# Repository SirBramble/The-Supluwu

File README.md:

# The Supluwu

A voltage converter for 3D printers.

## Motivation

When modifying a 3D printer, sometimes you need smaller Voltages to run for example a Raspberry PI or 12V Fans. Smaller buck converter modules are useful but can be hard to mount or connect multiple devices to. The Supluwu is a small board meant to fix this.

## Features

The Supluwu features 2 Voltage rails with 5V and 12V. Each Voltage Rail is capable of 5A and is spread out over 3 Terminals. The Input of each Rail is Fused with a 20mmx5mm glass fuse. The Input Voltage can be anything from 14-30V, so the typical 24V power supply of a 3D printer works fine. Each Terminal has a indicator LED, that lights up, if the buck converter is working properly.

## Heat Management

Heat Produced by the Regulator is spread out to the PCB and can be carried away by the PCB mounted [14mmx14mm heat sinks](https://www.amazon.de/-/en/gp/product/B09DKJPZRX?th=1).

## Pictures

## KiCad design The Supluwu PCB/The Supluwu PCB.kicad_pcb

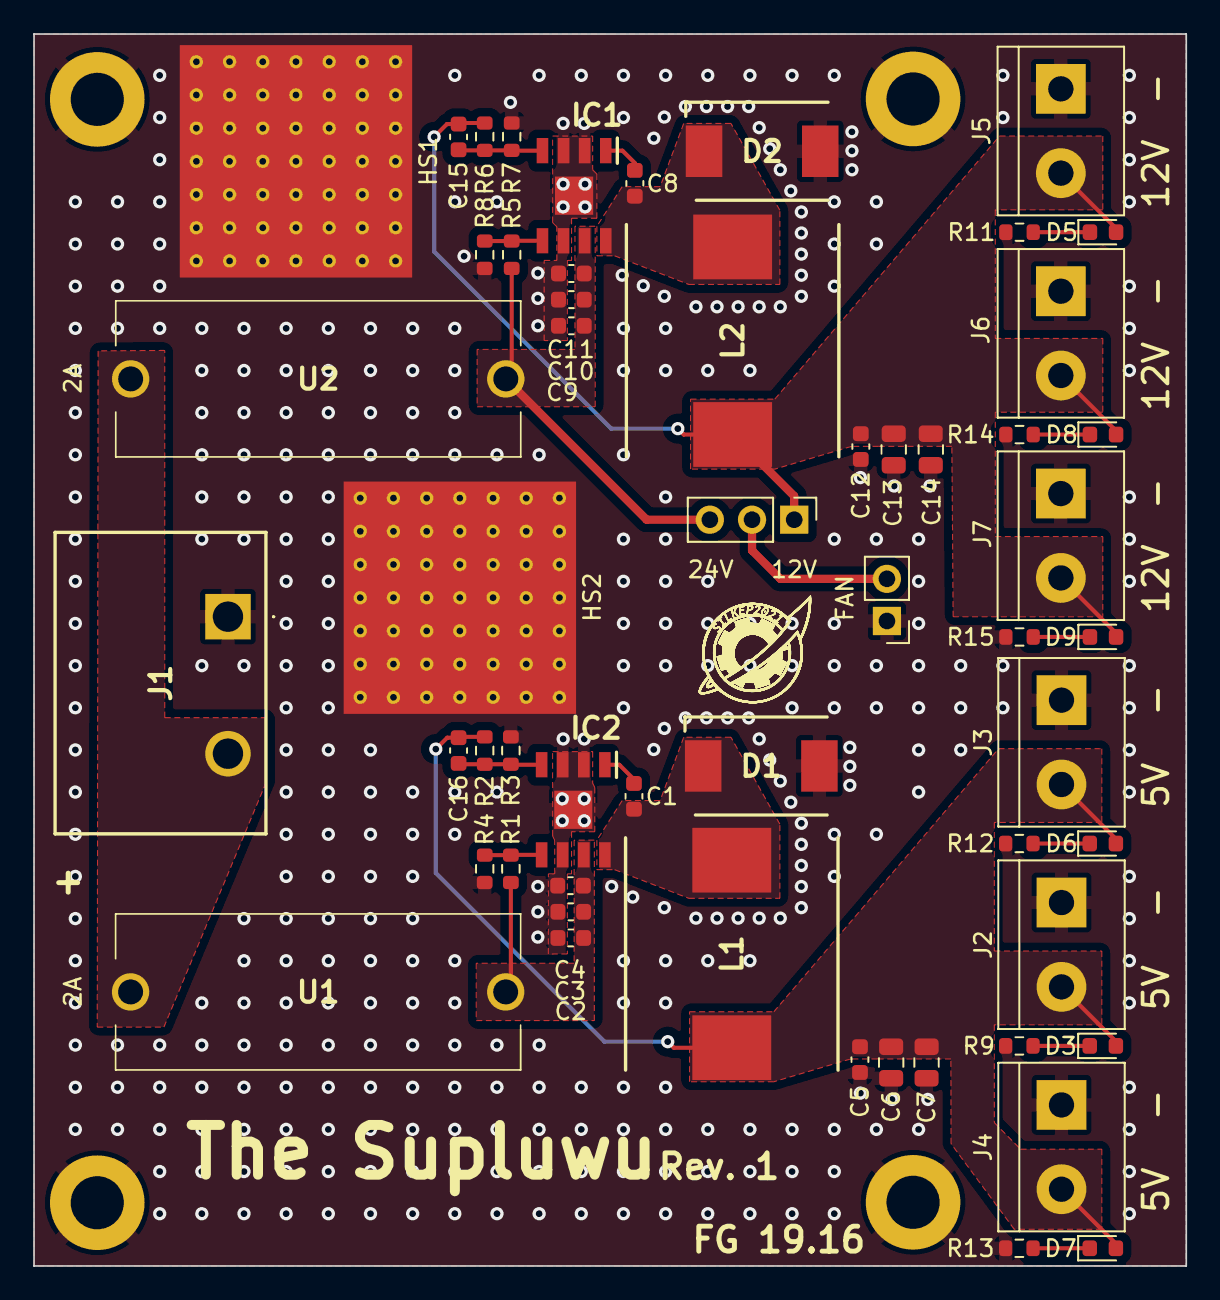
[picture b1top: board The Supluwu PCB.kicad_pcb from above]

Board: 2 copper layers, 69.4 x 74.2 mm, 59 parts (0 on the bottom side), 21 nets.

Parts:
C1, C8: 10nF; C_0603_1608Metric
C2, C3, C9, C10: 4u7; C_0603_1608Metric
C4, C5, C11, C12: 100n; C_0603_1608Metric
C6, C7, C13, C14: 22uF; C_0805_2012Metric
C15, C16: 82pF; C_0603_1608Metric
D1, D2: B550C-13-F; DIOM7959X250N
D3, D6, D7: LED_GREEN; LED_0603_1608Metric
D5, D8, D9: LED_Yellow; LED_0603_1608Metric
H1, H2, H3, H4: MountingHole_Pad; MountingHole_3.2mm_M3_ISO7380_Pad
HS1, HS2: Heatsink_Pad; 14x14mm PCB with VIA
IC1, IC2: RT6285GSP; SOIC127P600X175-9N
J1: 4DB-P107-02; 4DBP10702
J2, J3, J4, J5, J6, J7: 5V_OUT; TerminalBlock_bornier-2_P5.08mm
J8: V_Switch; PinHeader_1x03_P2.54mm_Vertical
J9: FAN; PinHeader_1x02_P2.54mm_Vertical
L1, L2: 15uH; INDPM140128X650N
R1, R4, R5, R8: DNP; R_0603_1608Metric
R2, R6: 100k; R_0603_1608Metric
R3: 31.6k; R_0603_1608Metric
R7: 11.3k; R_0603_1608Metric
R9, R12, R13: 1k; R_0603_1608Metric
R11, R14, R15: 3k3; R_0603_1608Metric
U1, U2: 0PTF0078P

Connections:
/5V Regulator/BOOT: C1.1, IC2.1 (BOOT)
/5V Regulator/EN: IC2.5 (EN), R1.2, R4.1
/5V Regulator/FB: C16.2, IC2.4 (FB), R2.2, R3.1
/5V Regulator/SW: C1.2, D1.1 (K), IC2.8 (SW), L1.1
/5V Regulator/VIN: C2.1, C3.1, C4.1, IC2.7 (VIN), R1.1, U1.2
/5V_OUT: C5.1, C6.1, C7.1, C16.1, D3.2 (A), D6.2 (A), D7.2 (A), J2.2, J3.2, J4.2, L1.2, R2.1
/12V Regulator/BOOT: C8.1, IC1.1 (BOOT)
/12V Regulator/EN: IC1.5 (EN), R5.2, R8.1
/12V Regulator/FB: C15.2, IC1.4 (FB), R6.2, R7.1
/12V Regulator/SW: C8.2, D2.1 (K), IC1.8 (SW), L2.1
/12V Regulator/VIN: C9.1, C10.1, C11.1, IC1.7 (VIN), J8.3, R5.1, U2.2
/12V_OUT: C12.1, C13.1, C14.1, C15.1, D5.2 (A), D8.2 (A), D9.2 (A), J5.2, J6.2, J7.2, J8.1, L2.2, R6.1
/24V_IN: J1.2, U1.1, U2.1
GND: C2.2, C3.2, C4.2, C5.2, C6.2, C7.2, C9.2, C10.2, C11.2, C12.2, C13.2, C14.2, D1.2 (A), D2.2 (A), H1.1, H2.1, H3.1, H4.1, HS1.1, HS2.1, IC1.2 (NC_1), IC1.3 (NC_2), IC1.6 (GND_1), IC1.9 (GND_2), IC2.2 (NC_1), IC2.3 (NC_2), IC2.6 (GND_1), IC2.9 (GND_2), J1.1, J2.1, J3.1, J4.1, J5.1, J6.1, J7.1, J9.1, R3.2, R4.2, R7.2, R8.2, R9.2, R11.2, R12.2, R13.2, R14.2, R15.2
unnamed: D3.1 (K), R9.1
unnamed: D5.1 (K), R11.1
unnamed: D6.1 (K), R12.1
unnamed: D7.1 (K), R13.1
unnamed: D8.1 (K), R14.1
unnamed: D9.1 (K), R15.1
unnamed: J8.2, J9.2

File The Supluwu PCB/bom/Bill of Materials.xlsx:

Designator | Footprint | Value | Description | Part Nr. | Quantity | Price/pcs. | Price
C1, C8 | 0603 | 10nF | 5% 50V Capacitor | 80-C0603C103J5RACTM | 2 | 9.2999999999999999E-2 | 0.186
C10, C2, C3, C9 | 0603 | 4u7 | 10% 25V Capacitor | 81-GRM188C81E475KE1D | 4 | 0.24199999999999999 | 0.96799999999999997
C11, C12, C4, C5 | 0603 | 100n | Generic 1% Capacitor | Generic | 4 | 0.01 | 0.04
C13, C14, C6, C7 | 0805 | 22uF | 20% 25V Capacitor | 187-CL21A226MAYNNWE | 4 | 0.29799999999999999 | 1.1919999999999999
C15, C16 | 0603 | 82pF | 5% 50V Capacitor | 581-06035A820JAT4A | 2 | 9.2999999999999999E-2 | 0.186
D1, D2 | DIOM7959X250N | B550C-13-F | 50V 5A Diode | 621-B550C-F | 2 | 0.52100000000000002 | 1.042
D3, D6, D7, | 0603 | LED_GREEN | Generic LED Greed | Generic | 3 | 0.05 | 0.15000000000000002
D5,D8,D9 | 0603 | LED_Yellow | Generic LED Yellow | Generic | 3 | 0.05 | 0.15000000000000002
IC1, IC2 | SOIC127P600X175-9N | RT6285GSP | 5A Buck Converter | 835-RT6285GSP | 2 | 0.83699999999999997 | 1.6739999999999999
J1 | 4DBP10702 | 4DB-P107-02 | Terminal Block Large | 571-14376676 | 1 | 0.73499999999999999 | 0.73499999999999999
J2, J3, J4, J5, J6, J7 | TerminalBlock_bornier-2_P5.08mm | 5V_OUT | Generic Terminal Block | Generic | 6 | 0.05 | 0.30000000000000004
J8 | PinHeader_1x03_P2.54mm_Vertical | V_Switch | Generic Pin Header | Generic | 1 | 0.05 | 0.05
J9 | PinHeader_1x02_P2.54mm_Vertical | FAN | Generic Pin Header | Generic | 1 | 0.05 | 0.05
L1, L2 | INDPM140128X650N | 15uH | 15uH 9A Inductor | 673-PA4343.153NLT | 2 | 1.66 | 3.32
R11, R14, R15 | 0603 | 3k3 | 1% Resistor | 603-RT0603FRE073K3L | 3 | 9.2999999999999999E-2 | 0.27900000000000003
R12, R13, R9 | 0603 | 1k | Generic 1% Resistor | Generic | 3 | 0.01 | 0.03
R2, R6 | 0603 | 100k | Generic 1% Resistor | Generic | 2 | 0.01 | 0.02
R3 | 0603 | 31.6k | 1% Resistor | 603-RT0603FRE0731K6L | 1 | 9.2999999999999999E-2 | 9.2999999999999999E-2
R7 | 0603 | 11.3k | 1% Resistor | 603-RT0603DRE0711K3L | 1 | 9.2999999999999999E-2 | 9.2999999999999999E-2
U1, U2 | 0PTF0078P | 0PTF0078P | Fuse Holder 5x20 | 576-0PTF0078P | 2 | 0.51200000000000001 | 1.024
 |  |  |  |  |  |  | 11.581999999999997

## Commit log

2023-12-29 added thumbnail
2023-12-30 added Schematic printout
2024-01-21 added 3D
